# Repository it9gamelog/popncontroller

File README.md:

# Pop'n Arcade Controller

Please see the video for the making of and some explaination:
https://github.com/it9gamelog/it9gamelog/wiki/Pop'n-Controller

# License

MIT License

# Software Requirements

* Firmware: Arduino 1.8.13 + Arduino Micro
* PCB: KiCad
* Mechanical: Solidworks

# Known Bugs

* The big button might have two M3 lugs on the side for asserting rotation motion, which the mechanical model didn't consider.

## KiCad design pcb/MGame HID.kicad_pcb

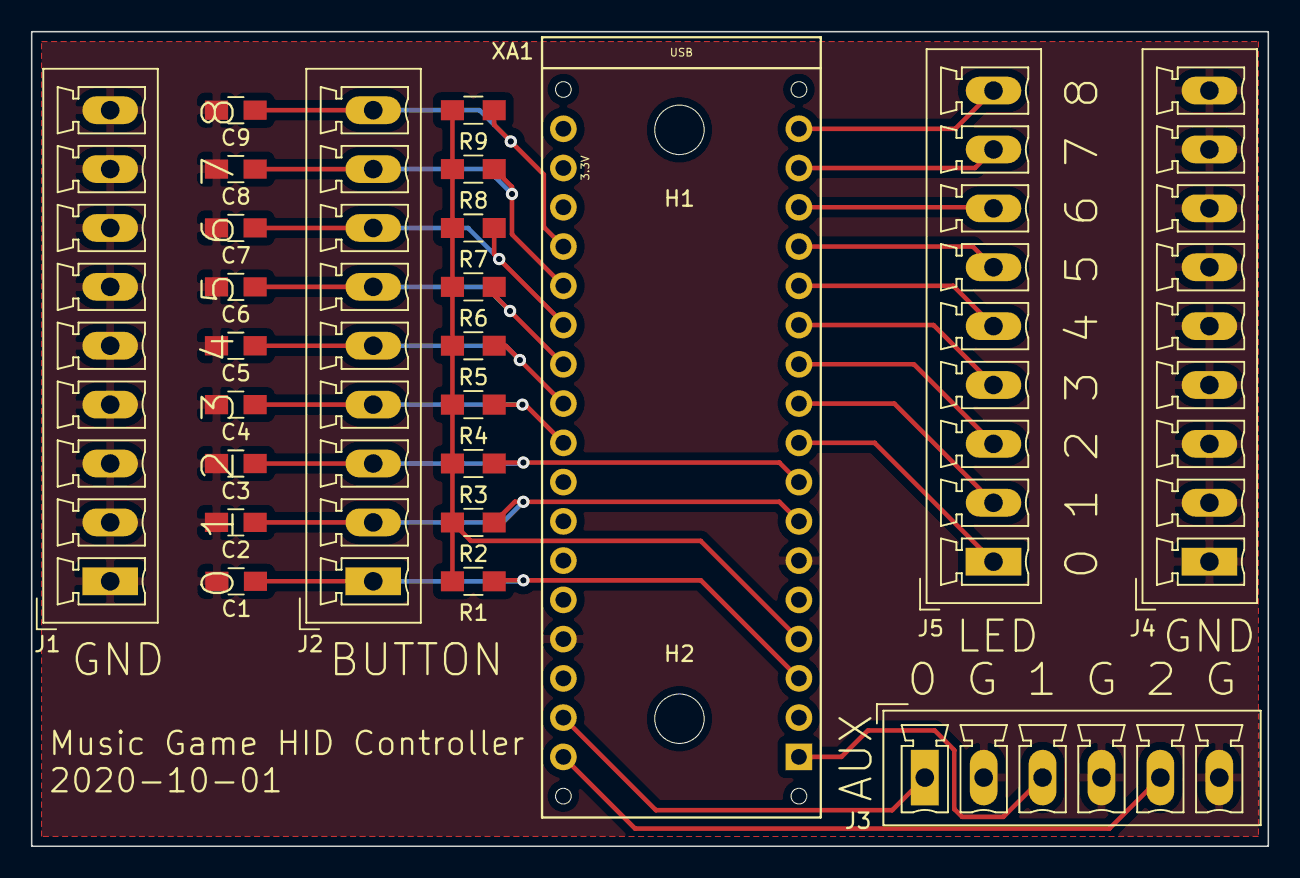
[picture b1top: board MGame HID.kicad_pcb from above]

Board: 2 copper layers, 80.0 x 52.7 mm, 26 parts (0 on the bottom side), 23 nets.

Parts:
C1, C2, C3, C4, C5, C6, C7, C8, C9: 20pF; C_0805_HandSoldering
H1, H2: MountingHole; MountingHole_3.2mm_M3
J1, J2, J4, J5: Conn_01x09; PhoenixContact_MCV-G_09x3.81mm_Vertical
J3: Conn_01x06; PhoenixContact_MCV-G_06x3.81mm_Vertical
R1, R2, R3, R4, R5, R6, R7, R8, R9: 680K; R_0805_HandSoldering
XA1: Arduino_Micro_Socket

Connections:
/AUX0: J3.1, XA1.MISO
/AUX1: J3.3, XA1.MOSI
/AUX2: J3.5, XA1.SCK
/BUT0: C1.1, J2.1, R1.2, XA1.D1
/BUT1: C2.1, J2.2, R2.2, XA1.D2
/BUT2: C3.1, J2.3, R3.2, XA1.D3
/BUT3: C4.1, J2.4, R4.2, XA1.A5
/BUT4: C5.1, J2.5, R5.2, XA1.A4
/BUT5: C6.1, J2.6, R6.2, XA1.A3
/BUT6: C7.1, J2.7, R7.2, XA1.A2
/BUT7: C8.1, J2.8, R8.2, XA1.A1
/BUT8: C9.1, J2.9, R9.2, XA1.A0
/LED0: J5.1, XA1.D4
/LED1: J5.2, XA1.D5
/LED2: J5.3, XA1.D6
/LED3: J5.4, XA1.D7
/LED4: J5.5, XA1.D8
/LED5: J5.6, XA1.D9
/LED6: J5.7, XA1.D10
/LED7: J5.8, XA1.D11
/LED8: J5.9, XA1.D12
GND: C1.2, C2.2, C3.2, C4.2, C5.2, C6.2, C7.2, C8.2, C9.2, J1.1, J1.2, J1.3, J1.4, J1.5, J1.6, J1.7, J1.8, J1.9, J3.2, J3.4, J3.6, J4.1, J4.2, J4.3, J4.4, J4.5, J4.6, J4.7, J4.8, J4.9, XA1.GND1, XA1.GND2
unnamed: R1.1, R2.1, R3.1, R4.1, R5.1, R6.1, R7.1, R8.1, R9.1, XA1.D0

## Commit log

2020-10-06 Create LICENSE
2020-10-07 Checking in all the works
2020-10-07 Ok a seemingly harmless last minute changes broke everything: missing pinMode in CapacitiveSensor code.
2020-10-07 HID: Emulate a joystick/joypad instead of keyboard
